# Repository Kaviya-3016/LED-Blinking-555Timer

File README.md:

# 💡 LED Blinking Circuit using 555 Timer (NE555 & LM555N Versions)

This repository contains two versions of an LED blinking circuit using 555 Timer ICs. The designs are created in Autodesk EAGLE and include both single-layer through-hole and double-layer SMD layouts.

---

## 📁 Project Versions

### 🔹 Single Layer – Through-Hole
- ✅ Timer IC: **LM555N**
- 📦 Components: Through-Hole
- 📐 PCB Type: Single Layer

**Files:**
- `Single_TH.sch` – Schematic (LM555N)
- `Singlr_TH.brd` – Board Layout
- Screeshot of Single layer Through Hole Schematic Sheet

- Screeshot of Single layer Through Hole Board Layout

---

### 🔹 Double Layer – SMD
- ✅ Timer IC: **NE555**
- 📦 Components: Surface Mount (SMD)
- 📐 PCB Type: Double Layer

**Files:**
- `Double_smd.sch` – Schematic (NE555)
- `Douuble_smd.brd` – Board Layout
- Screeshot of Double layer SMD Schematic Sheet
 
- Screeshot of Double layer SMD Board Layout

---

I also included **Bill Of Materials** of both Single Layer and Double Layer

---

## 🧰 Tools Used

- 🖥️ Autodesk EAGLE – PCB Design

---

## 📜 License

This project is licensed under the MIT License. See [LICENSE](LICENSE) for details.

---

## 📬 Let’s Connect

Feel free to connect with me on [LinkedIn](https://linkedin.com/in/kaviya-murugan) to explore more electronics projects!

---

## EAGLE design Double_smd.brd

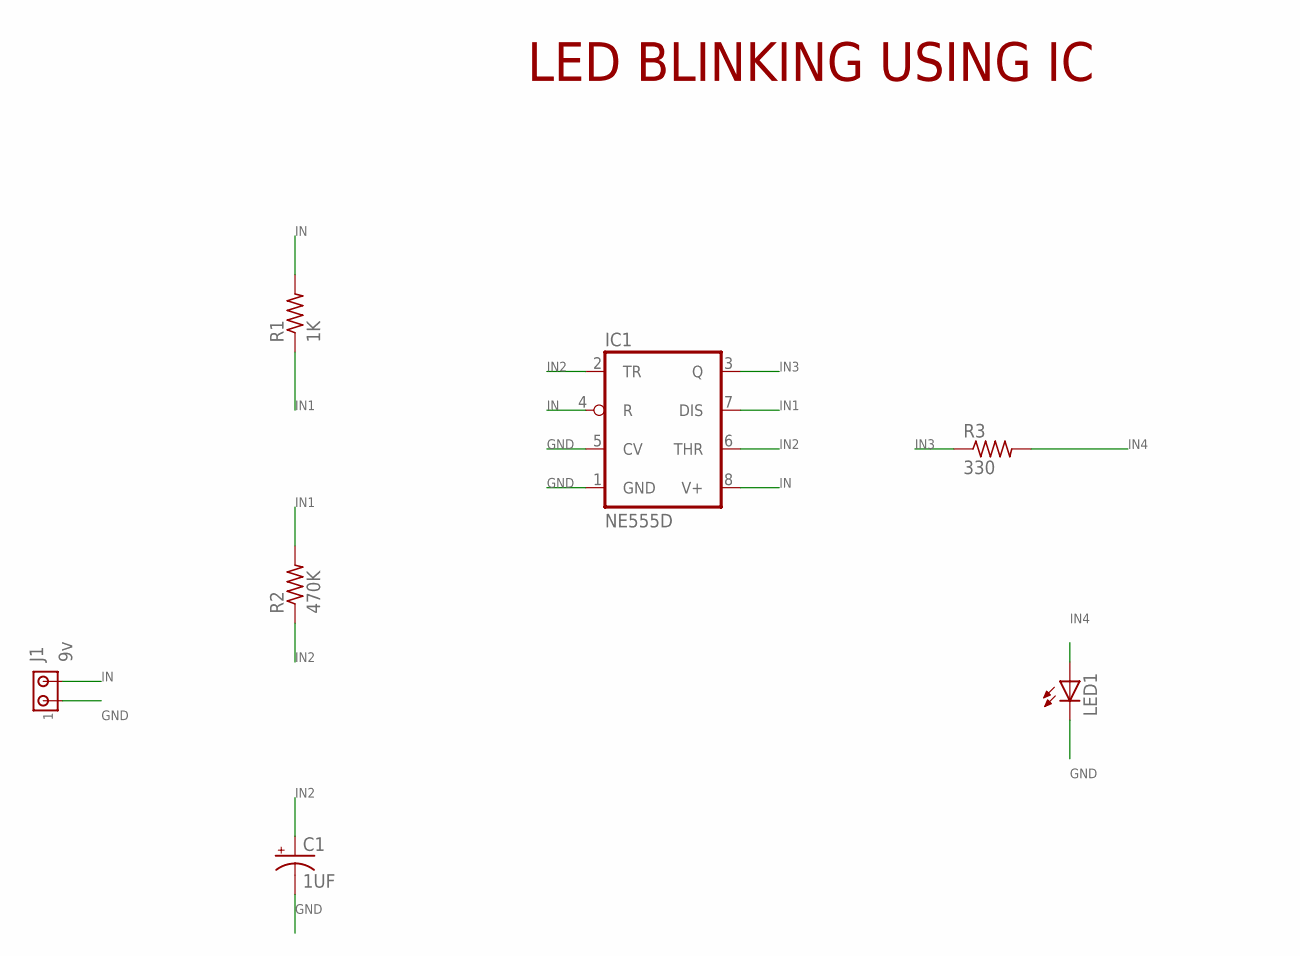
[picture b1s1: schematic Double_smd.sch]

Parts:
C1: 1UF; 085CS_1R
IC1: NE555D; SO08
J1: 9v; 1X2MTA
LED1: LED5MM
R1: 1K; R0805
R2: 470K; R0805
R3: 330; R0805

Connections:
GND: C1.-, IC1.1 (GND), IC1.5 (CV), J1.1, LED1.K (C)
IN: IC1.4 (R), IC1.8 (V+), J1.2, R1.2
IN1: IC1.7 (DIS), R1.1, R2.2
IN2: C1.+, IC1.2 (TR), IC1.6 (THR), R2.1
IN3: IC1.3 (Q), R3.1
IN4: LED1.A, R3.2

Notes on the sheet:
LED BLINKING USING IC

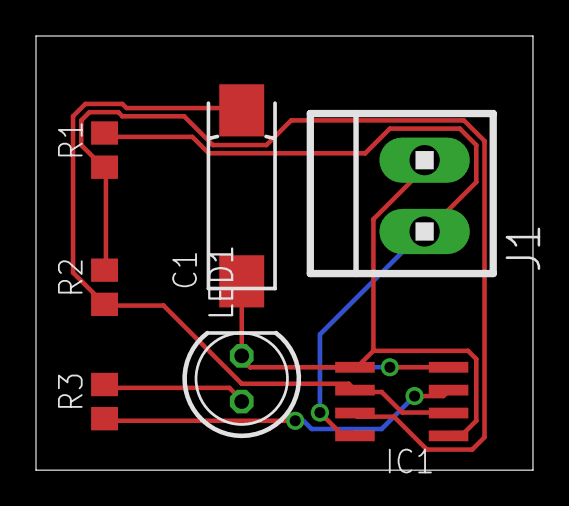
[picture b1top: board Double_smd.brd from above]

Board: 2 copper layers, 27.6 x 24.1 mm, 7 parts (0 on the bottom side), 6 nets.
